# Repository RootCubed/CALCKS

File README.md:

# CALCKS
An open-source calculator I made for a school finals project.

## Hardware
All hardware files to make your own CALCKS are in this repository. The PCB design files can be opened with [KiCad](https://kicad.org/). The case can be 3D printed with the files found in <Hardware/3D Models>.

## Building
To compile this project for AVR architecture, you will need the GCC suite for AVR. For Windows, I used [WinAVR](http://winavr.sourceforge.net/).
`cd` into the Firmware directory of your locally cloned repository and run `make eeprom upload`. You might need to adjust the used COM port in the Makefile to get avrdude working.

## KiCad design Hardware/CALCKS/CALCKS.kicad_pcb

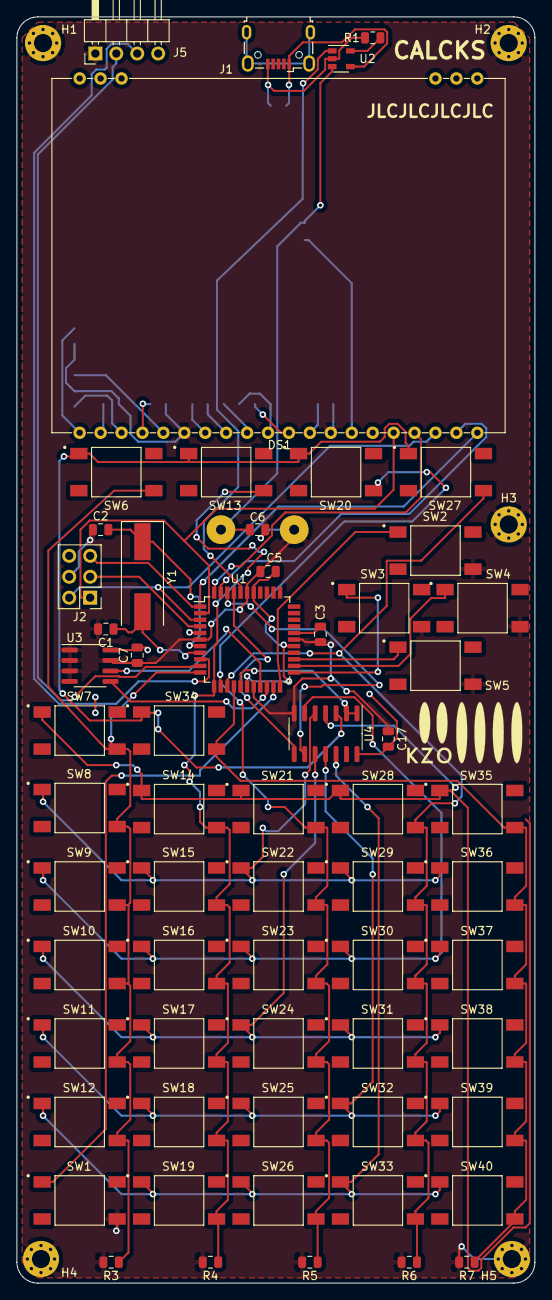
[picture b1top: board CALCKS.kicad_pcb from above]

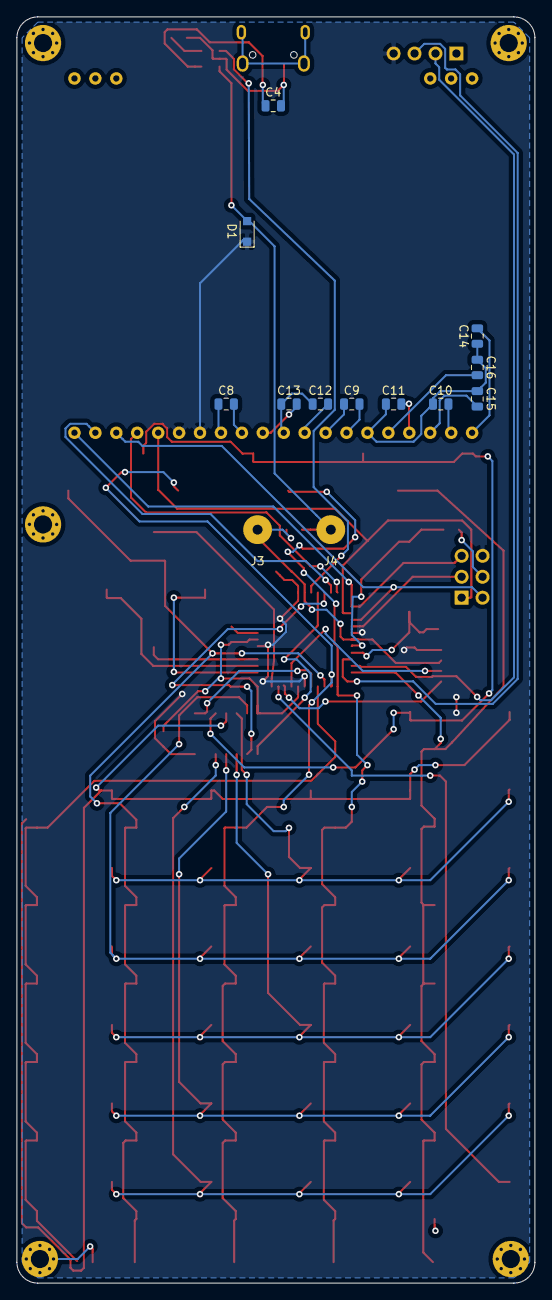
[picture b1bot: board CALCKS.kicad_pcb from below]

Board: 2 copper layers, 62.9 x 153.7 mm, 80 parts (13 on the bottom side), 51 nets.

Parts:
C1, C2: 30pF; C_0805_2012Metric
C3, C5, C7, C17: 0.1uF; C_0805_2012Metric
C4, C6: 4.7uF; C_0805_2012Metric
C8, C9, C10, C11, C12, C13, C14, C15, C16: 1uF; C_0805_2012Metric
D1: D; D_SOD-323_HandSoldering
DS1: DOGM128-6; LCD_DOGM128-6
H1, H2, H3, H4, H5: MountingHole_Pad; MountingHole_2.2mm_M2_Pad_Via
J1: USB_B_Micro; USB_Micro-B_Wuerth_629105150521
J2: Conn_02x03_Counter_Clockwise; PinHeader_2x03_P2.54mm_Vertical
J3, J4: Conn_01x01_Male; SolderWirePad_1x01_Drill1.2mm
J5: Conn_01x04_Male; PinHeader_1x04_P2.54mm_Horizontal
R1: 3.3k; R_0805_2012Metric
R3, R4, R5, R6, R7: 220; R_0805_2012Metric
SW1, SW2, SW3, SW4, SW5, SW6, SW7, SW8, SW9, SW10, SW11, SW12, SW13, SW14, SW15, SW16, SW17, SW18, SW19, SW20, SW21, SW22, SW23, SW24, SW25, SW26, SW27, SW28, SW29, SW30, SW31, SW32, SW33, SW34, SW35, SW36, SW37, SW38, SW39, SW40: SW_Push_Dual; SW_TL3301SPF260QG
U1: ATmega1284-AU; TQFP-44_10x10mm_P0.8mm
U2: MCP73831-2-OT; SOT-23-5
U3: AT24CS64-SSHM; SOIC-8_3.9x4.9mm_P1.27mm
U4: 74HC164; SOIC-14_3.9x8.7mm_P1.27mm
Y1: 8MHz; Crystal_SMD_HC49-SD

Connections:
+BATT: C6.2, D1.2, J4.1, U2.3
-BATT: C1.2, C2.1, C3.1, C5.1, C6.1, C7.1, C8.1, C10.1, C11.1, C14.1, C15.1, C16.1, C17.1, DS1.26, DS1.33, H1.1, H2.1, H3.1, H4.1, H5.1, J2.4, J3.1, J5.1, R3.2, R4.2, R5.2, R6.2, R7.2, SW1.4, SW2.4, SW3.4, SW4.4, SW5.4, U1.6, U1.18, U1.28, U1.39, U3.1, U3.2, U3.3, U3.4, U3.7, U4.7
BATT_STATUS: U1.40, U2.1
BTN_AB: U1.16, U4.1, U4.2
BTN_ROW1: R3.1, SW6.4, SW7.4, SW8.4, SW9.4, SW10.4, SW11.4, SW12.4, U1.11
BTN_ROW2: R4.1, SW13.4, SW14.4, SW15.4, SW16.4, SW17.4, SW18.4, SW19.4, U1.12
BTN_ROW3: R5.1, SW20.4, SW21.4, SW22.4, SW23.4, SW24.4, SW25.4, SW26.4, U1.13
BTN_ROW4: R6.1, SW27.4, SW28.4, SW29.4, SW30.4, SW31.4, SW32.4, SW33.4, U1.14
BTN_ROW5: R7.1, SW34.4, SW35.4, SW36.4, SW37.4, SW38.4, SW39.4, SW40.4, U1.15
CLK: U1.41, U4.8
CLR: U1.42, U4.9
MISO: DS1.36, J2.1, U1.2
MOSI: DS1.40, J2.5, U1.1
unnamed: C1.1, U1.8, Y1.2
unnamed: C2.2, U1.7, Y1.1
unnamed: C3.2, U1.29
unnamed: C4.1, J1.1, U2.4
unnamed: C4.2, J1.5, R1.1, U2.2
unnamed: C8.2, DS1.32
unnamed: C9.1, DS1.28
unnamed: C9.2, DS1.27
unnamed: C10.2, DS1.22
unnamed: C11.2, DS1.24
unnamed: C12.1, C13.1, DS1.30
unnamed: C12.2, DS1.29
unnamed: C13.2, DS1.31
unnamed: C14.2, DS1.21
unnamed: C15.2, DS1.23
unnamed: C16.2, DS1.25
unnamed: R1.2, U2.5
unnamed: SW1.1, U1.21
unnamed: SW2.1, U1.22
unnamed: SW3.1, U1.23
unnamed: SW4.1, U1.24
unnamed: SW5.1, U1.25
unnamed: SW10.1, SW17.1, SW24.1, SW31.1, SW38.1, U4.10
unnamed: SW11.1, SW18.1, SW25.1, SW32.1, SW39.1, U4.11
unnamed: SW12.1, SW19.1, SW26.1, SW33.1, SW40.1, U4.12
unnamed: SW6.1, SW13.1, SW20.1, SW27.1, SW34.1, U4.3
unnamed: SW7.1, SW14.1, SW21.1, SW28.1, SW35.1, U4.4
unnamed: SW8.1, SW15.1, SW22.1, SW29.1, SW36.1, U4.5
unnamed: SW9.1, SW16.1, SW23.1, SW30.1, SW37.1, U4.6
unnamed: U1.19, U3.6
unnamed: U1.20, U3.5
RESET: J2.3, U1.4
RST: DS1.39, U1.43
RXD0: J5.3, U1.9
SCK: DS1.38, J2.2, U1.3
SCL: DS1.37, U1.44
TXD0: J5.2, U1.10
VCC: C5.2, C7.2, C17.2, D1.1, DS1.34, DS1.35, J2.6, J5.4, U1.5, U1.17, U1.27, U1.38, U3.8, U4.14

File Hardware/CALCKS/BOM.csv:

Reference, Quantity, Value, Footprint, Datasheet
C14 C10 C15 C11 C16 C9 C12 C13 C8 ,9,"1uF","Capacitor_SMD:C_0805_2012Metric","~"
C2 C1 ,2,"30pF","Capacitor_SMD:C_0805_2012Metric","~"
C5 C7 C17 C3 ,4,"0.1uF","Capacitor_SMD:C_0805_2012Metric","~"
C6 C4 ,2,"4.7uF","Capacitor_SMD:C_0805_2012Metric","~"
D1 ,1,"D","Diode_SMD:D_SOD-323_HandSoldering","~"
DS1 ,1,"DOGM128-6","CALCKS:LCD_DOGM128-6",""
H1 H2 H3 H4 H5 ,5,"MountingHole_Pad","MountingHole:MountingHole_2.2mm_M2_Pad_Via","~"
J1 ,1,"USB_B_Micro","Connector_USB:USB_Micro-B_Wuerth_629105150521","~"
J2 ,1,"Conn_02x03_Counter_Clockwise","Connector_PinHeader_2.54mm:PinHeader_2x03_P2.54mm_Vertical","~"
J3 J4 ,2,"Conn_01x01_Male","Connector_Wire:SolderWirePad_1x01_Drill1.2mm","~"
J5 ,1,"Conn_01x04_Male","Connector_PinHeader_2.54mm:PinHeader_1x04_P2.54mm_Horizontal","~"
R1 ,1,"3.3k","Resistor_SMD:R_0805_2012Metric","~"
R6 R5 R4 R7 R3 ,5,"220","Resistor_SMD:R_0805_2012Metric","~"
SW6 SW13 SW20 SW27 SW34 SW7 SW14 SW21 SW28 SW35 SW8 SW15 SW22 SW29 SW36 SW9 SW16 SW23 SW30 SW37 SW10 SW17 SW24 SW31 SW38 SW11 SW18 SW25 SW32 SW39 SW12 SW19 SW26 SW40 SW1 SW2 SW3 SW4 SW5 SW33 ,40,"SW_Push_Dual","Downloaded Footprints:SW_TL3301SPF260QG","~"
U1 ,1,"ATmega1284-AU","Package_QFP:TQFP-44_10x10mm_P0.8mm","http://ww1.microchip.com/downloads/en/DeviceDoc/Atmel-8272-8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"
U2 ,1,"MCP73831-2-OT","Package_TO_SOT_SMD:SOT-23-5","http://ww1.microchip.com/downloads/en/DeviceDoc/20001984g.pdf"
U3 ,1,"AT24CS64-SSHM","Package_SO:SOIC-8_3.9x4.9mm_P1.27mm","http://ww1.microchip.com/downloads/en/DeviceDoc/Atmel-8870-S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"
U4 ,1,"74HC164","Package_SO:SOIC-14_3.9x8.7mm_P1.27mm","https://assets.nexperia.com/documents/data-sheet/74HC_HCT164.pdf"
Y1 ,1,"8MHz","Crystal:Crystal_SMD_HC49-SD","~"

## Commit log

2020-05-06 Add files
2020-05-06 create license and README
2020-05-06 add some math characters
2020-05-06 Add buttons for temporary support for a new button
2020-05-07 First few steps in Autodesk EAGLE
2020-05-07 Update gitignore
2020-05-09 Font expansion + button overlay
2020-05-09 small bug fixes
2020-05-09 start support for math operations
2020-05-09 changed font slightly
2020-05-09 work on doCalculation
2020-05-14 remove unused code, small bug fix
2020-05-14 working simple operands
2020-05-16 Restructure entire system, compile with Makefile
2020-05-16 Initial commit for web emulator
2020-05-17 Upload EEPROM data via UART/USB
2020-05-17 Add some more info about the project
2020-05-17 Graphics: generate binary instead of header files
2020-05-17 move to Firmware project
2020-05-17 make buttons look a bit nicer
2020-05-17 Automate generating graphics binary
2020-05-17 Make VS Code not complain
2020-05-19 Tweak button appearance
2020-05-21 Remove header comments
2020-05-21 Shift 8x16 font upwards, add '-' and '.'
2020-05-21 Don't include exe or graphics file
2020-05-21 Add additional characters to header file
2020-05-21 Combine some display functions, make some new ones
2020-05-21 Remove __AVR_ATmega328P__ header
2020-05-21 Use new GUI functions in the firmware
2020-05-26 start work on menus
2020-05-26 Start a sketch of the hardware design
2020-06-26 Add PCB progress from yesterday
2020-06-28 PCB routing
2020-06-30 small changes
2020-06-30 Final changes to PCB before sending it off
2020-08-28 Version 2 of PCB
2020-08-30 Make sure all function names are in snake_case
2020-08-30 Start work on expression parsing Currently, terms with +, -, * and / are able to be parsed.
2020-08-31 Continued work on the term parser Parsing expressions with multiple equivalent operators now works Added ability to evaluate the expression
2020-09-01 Various changes for upgrading to PCB
2020-09-01 forgot this file
2020-09-02 fix merge issues, increase baud rate
2020-09-02 Re-add version 2 of Hardware
2020-09-02 Use term.c for parsing, read Vcc
2020-09-02 Make buttons.c compatible with new hardware
2020-09-02 add term.c
2020-09-03 Start working on sleep mode
2020-09-04 some small changes - added bmp388 (currently commented out) - Charging / not charging
2020-09-09 Add more buttons, remove some debugging
2020-09-09 Add some new GUI functions - set pixel - draw line - draw rectangle - draw circle - clear rectangle
2020-09-09 Apply to console project
2020-09-09 Lots of new features - state management for menus and other screens - draw mandelbrot - draw graphs
2020-09-09 Make terms work if just one number was entered
2020-10-12 Able to parse brackets, improve battery display
2020-10-12 remove unused code, more graphics bounds checks
2020-10-12 Add more buttons to emulator
2020-10-12 Make button related things more extensible
2020-10-12 Move term input to separate file
2020-10-13 Begin work on equation solver
2020-10-16 Restructure a lot of things, add info screen
2020-10-16 Add exponent operation
2020-10-25 Fix buffer overflow in bufStr
2020-10-27 Support for decimals, add button grid SVG
2020-10-28 add cursor blink, term redraw, term input in graph
2020-10-28 add arrow characters
2020-10-28 create define statements for special characters
2020-11-01 Many bug fixes, added scrolling in term - Sometimes, the emulator showed certain pixel arrangements incorrectly: The root cause of this was that when the buffer contained 0x0A, the emulator would out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
2020-11-01 Comment out GUI test
2020-11-01 Add back tab buttons
2020-11-01 fix battery icon
2020-11-01 Move cursor blinking to mathinput, refactor solver
2020-11-01 Add used RAM info for memory leak checking
2020-11-01 Add quadratic solver
2020-11-02 Add delete button & a couple of bug fixes
2020-11-02 Fix displaying of inverted characters
2020-11-02 Add latest 3D models
2020-11-02 Fix edge case with brackets
2020-11-02 Make compilation work on linux
2020-11-02 Quick bug fix for delete button
2020-11-03 Fix Makefile for Windows
2020-11-03 Term syntax checking in main screen
2020-11-03 Fix bug in syntax checking & add it to all menus
2020-11-05 Syntax checking fix, (maybe?) fix memory leak
2020-11-23 use regular threads instead of windows threads
2020-11-23 Some small bug fixes
2020-11-23 Get project to compile with Linux and Windows
2021-05-08 Big refactor of the term parser Other additions include: - Calculator goes to sleep after two minutes - RAM stats in info screen
2021-05-08 Add trigonometric function buttons
2021-05-08 Add unit tests for term parsing
2021-05-08 Expand README
2021-05-08 Fix bug in unit test, simplify dummy operations
2021-05-10 Fix server not killing calc process
2021-05-10 Bump socket.io from 2.3.0 to 2.4.0 in /Firmware/server
    Bumps [socket.io](https://github.com/socketio/socket.io) from 2.3.0 to 2.4.0.
    - [Release notes](https://github.com/socketio/socket.io/releases)
    - [Changelog](https://github.com/socketio/socket.io/blob/2.4.0/CHANGELOG.md)
    - [Commits](https://github.com/socketio/socket.io/compare/2.3.0...2.4.0)
2021-05-11 Add cos and tan to term parser
2021-11-05 Update npm modules
2021-11-05 Remove binsend and update eepromgen modules
2021-11-06 Update website
2021-11-06 Fix some compiler warnings
2021-11-06 Convert online version to WASM
2021-11-08 Fix graph view
2021-11-08 Fix key input for button presses
2021-11-08 Build object files in respective folders
2021-11-09 More characters
2021-11-09 Add new characters to gui.h
2021-11-09 Update EEPROM font char number
2021-11-09 Add UART functionality
2021-11-09 Add "apps"
2021-11-09 Rework mathinput
2021-11-09 Update Makefile
2021-11-09 Fix applist_buttonPress
2021-11-09 Fix path in EEPROM generator
2021-11-09 Add sources for paper
2021-11-09 Fix AVR code
2021-11-10 Fix test makefile
2021-11-12 Create gui_clear_screen function
2021-11-13 Create exception handling system
2022-08-11 Make links in TOC clickable
2022-11-09 Bump socket.io-parser from 4.0.4 to 4.0.5 in /Firmware/server
    Bumps [socket.io-parser](https://github.com/socketio/socket.io-parser) from 4.0.4 to 4.0.5.
    - [Release notes](https://github.com/socketio/socket.io-parser/releases)
    - [Changelog](https://github.com/socketio/socket.io-parser/blob/main/CHANGELOG.md)
    - [Commits](https://github.com/socketio/socket.io-parser/compare/4.0.4...4.0.5)
    ---
    updated-dependencies:
2022-11-22 Bump engine.io and socket.io in /Firmware/server
    Bumps [engine.io](https://github.com/socketio/engine.io) to 6.2.1 and updates ancestor dependency [socket.io](https://github.com/socketio/socket.io). These dependencies need to be updated together.
    Updates `engine.io` from 6.0.0 to 6.2.1
    - [Release notes](https://github.com/socketio/engine.io/releases)
    - [Changelog](https://github.com/socketio/engine.io/blob/main/CHANGELOG.md)
    - [Commits](https://github.com/socketio/engine.io/compare/6.0.0...6.2.1)
    Updates `socket.io` from 4.3.1 to 4.5.3
2022-12-08 Bump qs and express in /Firmware/server
    Bumps [qs](https://github.com/ljharb/qs) to 6.11.0 and updates ancestor dependency [express](https://github.com/expressjs/express). These dependencies need to be updated together.
    Updates `qs` from 6.7.0 to 6.11.0
    - [Release notes](https://github.com/ljharb/qs/releases)
    - [Changelog](https://github.com/ljharb/qs/blob/main/CHANGELOG.md)
    - [Commits](https://github.com/ljharb/qs/compare/v6.7.0...v6.11.0)
    Updates `express` from 4.17.1 to 4.18.2
2022-12-14 Bump express from 4.17.1 to 4.17.3 in /Firmware/server
    Bumps [express](https://github.com/expressjs/express) from 4.17.1 to 4.17.3.
    - [Release notes](https://github.com/expressjs/express/releases)
    - [Changelog](https://github.com/expressjs/express/blob/master/History.md)
    - [Commits](https://github.com/expressjs/express/compare/4.17.1...4.17.3)
    ---
    updated-dependencies:

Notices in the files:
Hardware/CALCKS/CALCKS.kicad_pcb:
License: MIT
